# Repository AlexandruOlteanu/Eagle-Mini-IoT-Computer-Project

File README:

<Copyright Alexandru Olteanu, grupa 332CA, alexandruolteanu2001@gmail.com>

    Proiectul a fost unul interesant, nu regret ca am invatat cat de cat cum 
se proiecteaza o placuta. Schema a fost relativ usor de construit, doar 
unele componente precum Pinhead-ul cu 6 pini au trebuit luate din alte 
biblioteci, In rest procesul a mers destuld e ok.
    La construirea board-ului a fost mai mult de lucru, a durat ceva pana
am pus dimensiunile placutei, unde vin gaurile si usb-ul ce iese afara, apoi
punerea strategica a componentelor incat:
    a) sa incapa
    b) condensatoarele sa fie apropiate de pinii majoritatii componentelor la 
care sunt conectati
    c) Fiecare rezistenta sa fie pusa cat mai central intre componentele legate
la ea.
    In continuarea, la tragerea cablurilor a fost nevoie de mai multe rectificari
pana sa ajung la varianta finala, am avut diverse probleme de overlap, fire care
nu mai mergeau trase din cauza altora, etc.
    Per total, o tema faina dar muncitoreasca, thx!

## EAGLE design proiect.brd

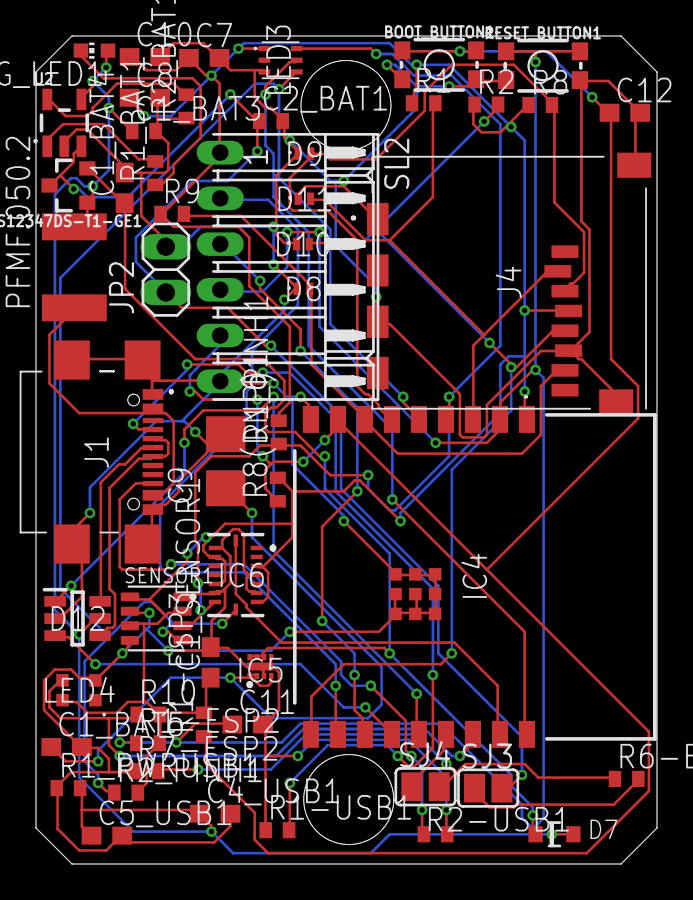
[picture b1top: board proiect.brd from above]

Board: 2 copper layers, 34.5 x 46.0 mm, 54 parts (0 on the bottom side), 32 nets.

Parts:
BOOT_BUTTON1: ESP32_WROVER_SPARKFUN-SWITCHES_TACTILE_SWITCH_SMD_4.6X2.8MM
C1_BAT3, C2_BAT1: 4.7uF; ESP32_WROVER_EAGLE-LTSPICE_C0402
C1_BAT4, C1_BAT5, C5_USB1: 4.7uF; ESP32_WROVER_RCL_C0603
C1_SENSOR1, C4_USB1, C7, C8, C10, C12: 100nF; ESP32_WROVER_RCL_C0603
C9: 100uF TANT; RCL_CT3528
C11: 1uF; ESP32_WROVER_RCL_C0603
CHG_LED1: ESP32_WROVER_ADAFRUIT_CHIP-LED0603
D7: ESP32_WROVER_AVX---SD0805S020S1R0_AVX_SD0805S020S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; ESP32_WROVER_AVX---SD0805S020S1R0_AVX_SD0805S020S1R0_0
D8, D9, D10, D11: PESD3V3S1BLYL; SAMACSYS_PARTS_PESD5V0S1BL315
D12: USBLC6-2SC6Y; SAMACSYS_PARTS_SOT95P280X145-6N
IC4: ESP32-C3-WROOM-02-H4; SAMACSYS_PARTS_ESP32C3WROOM02H4
IC5: NCP186BMX330TAG; SAMACSYS_PARTS_NCP186AMX330TAG
IC6: BMI085; SAMACSYS_PARTS_BMI085
J1: USB4110-GF-A; SAMACSYS_PARTS_USB4110GFA
J4: 112A-TAAR-R03_ATTEND; SAMACSYS_PARTS_112ATAARR03ATTEND
JP2: PINHEAD_1X02
LED3: LTR308; ESP32_WROVER_SAMACSYS_PARTS_LTR303ALS01
LED4: WS2812B-2020; SAMACSYS_PARTS_WS2812B2020
PFMF.050.2: 500mA; ESP32_WROVER_VARISTOR_CT/CN1812
R1, R1-ESP2, R1-ESP3, R2, R2_PINH1, R8, R8(DNP)1, R9, R10: 10K; ESP32_WROVER_EAGLE-LTSPICE_R0402
R1-USB1, R2-USB1: 5K1; ESP32_WROVER_EAGLE-LTSPICE_R0402
R1_BAT1: 200; ESP32_WROVER_EAGLE-LTSPICE_R0402
R1_PINH1: 10k; ESP32_WROVER_EAGLE-LTSPICE_R0402
R1_PWRUSB1, R6-ESP2, R7-ESP2: 100K; ESP32_WROVER_EAGLE-LTSPICE_R0402
R2_BAT1: 2K; ESP32_WROVER_EAGLE-LTSPICE_R0402
RESET_BUTTON1: ESP32_WROVER_SPARKFUN-SWITCHES_TACTILE_SWITCH_SMD_4.6X2.8MM
S12347DS-T1-GE1: 20V/4.2A/52mΩ/1.4W; ESP32_WROVER_SPARKFUN-DISCRETESEMI_SOT23-3
SENSOR1: BME680; ESP32_WROVER_BME680_PSON80P300X300X100-8N
SJ3, SJ4: JUMPER_SJ
SL2: 06PA
U2: MCP73831; ESP32_WROVER_SPARKFUN-IC-POWER_SOT23-5

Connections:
3V1: C1_SENSOR1.1, C7.1, C8.1, C10.1, IC4.1, IC6.3, IC6.7, IC6.11, IC6.14, J4.P4, LED3.1, LED4.4, R1.1, R1-ESP2.2, R1-ESP3.2, R1_PINH1.2, R2.1, R2_PINH1.2, R8.1, R8(DNP)1.2, R9.1, R10.2, SENSOR1.2, SENSOR1.6, SENSOR1.8, SL2.1
A2: IC4.15, SJ4.1
BOOT1: BOOT_BUTTON1.3, BOOT_BUTTON1.4, C12.1, IC4.8, R1-ESP3.1, R8(DNP)1.1, SL2.5
D+1: D12.1, IC4.14
D-1: D12.3, IC4.13
DN1: D12.4, J1.A7, J1.B7
DP1: D12.6, J1.A6, J1.B6
GND1: BOOT_BUTTON1.1, BOOT_BUTTON1.2, C1_BAT3.2, C1_BAT4.2, C1_BAT5.2, C1_SENSOR1.2, C2_BAT1.2, C4_USB1.2, C5_USB1.2, C7.2, C8.2, C9.-, C10.2, C11.2, C12.2, D8.1, D9.1, D10.1, D11.1, D12.2, IC4.9, IC4.19, IC4.20, IC4.21, IC4.22, IC4.23, IC4.24, IC4.25, IC4.26, IC4.27, IC5.3, IC5.5, IC5.9, IC6.4, IC6.6, IC6.10, IC6.15, J1.A1, J1.A12, J1.B1, J1.B12, J1.MP1, J1.MP2, J1.MP3, J1.MP4, J4.G1, J4.G2, J4.G3, J4.G4, J4.P6, JP2.2, LED3.3, LED4.2, R1-USB1.1, R1_PWRUSB1.1, R2-USB1.2, R2_BAT1.1, R7-ESP2.1, RESET_BUTTON1.1, RESET_BUTTON1.2, SENSOR1.1, SENSOR1.5, SENSOR1.7, SL2.6, U2.2
GPIO2: IC4.18, LED3.5
GPIO3: IC4.17, IC6.16
MISO1: D8.2, IC4.7, J4.P7, R9.2
MOSI1: D9.2, IC4.6, J4.P3, R8.2
unnamed: J1.A5, R1-USB1.2
unnamed: J1.B5, R2-USB1.1
unnamed: C1_BAT4.1, D7.1, IC5.6, IC5.7, IC5.8, S12347DS-T1-GE1.2
unnamed: C1_BAT5.1, C9.+, IC5.1, IC5.2, IC5.4
unnamed: R6-ESP2.2, SJ3.1
unnamed: R6-ESP2.1, R7-ESP2.2, SJ4.2
unnamed: R1_BAT1.2, U2.1
unnamed: CHG_LED1.C, R1_BAT1.1
unnamed: R2_BAT1.2, U2.5
NEOPIXEL1: IC4.16, LED4.3, R10.1
RESET1: C11.1, IC4.2, R1-ESP2.1, RESET_BUTTON1.3, RESET_BUTTON1.4, SL2.4
RX1: IC4.11, SL2.2
SCK1: D10.2, IC4.10, J4.P5, R2.2
SCL1: IC4.5, IC6.8, LED3.4, R2_PINH1.1, SENSOR1.4
SDA1: IC4.4, IC6.9, LED3.6, R1_PINH1.1, SENSOR1.3
SS1: D11.2, IC4.3, J4.P2, R1.2
TX1: IC4.12, SL2.3
VBAT1: C2_BAT1.1, JP2.1, S12347DS-T1-GE1.3, SJ3.2, U2.3
VBUS1: C1_BAT3.1, C4_USB1.1, C5_USB1.1, CHG_LED1.A, D7.2, D12.5, PFMF.050.2.2, R1_PWRUSB1.2, S12347DS-T1-GE1.1, U2.4
VUSB1: J1.A4, J1.A9, J1.B4, J1.B9, PFMF.050.2.1
